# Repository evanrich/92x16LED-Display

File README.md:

#92x16LED-Display

Custom made scrolling LED sign 92 dots wide by 16 tall.

This is going to be the repository for my latest project, a 96x16 LED sign.  

The sign consists of the following:
4x Sure 3216 LED Matrix Displays
1x Custom controller board with bluetooth capabilities to communicate with the Sign
1x Custom power board to deliver 6A to the sign from a 12V source (my car)
Custom cut Acrylic plastic along with various screws to mount and display the sign.

**If you want to see how-to instructions on how to assemble this, please look in the Wiki for a complete guide on how to build this sign**

Please feel free to contact me at evanrich81[at]gmail.com if you have any questions

**UPDATES** <br />
* 5/23/13 - Redesigned controller board. Board sent to fab, uploaded BOM/Datasheets for controller
* 5/5/13 - Created Repository, will begin adding things to it when I have the time.

**Source code, BOMs, Etc**

* https://github.com/evanrich/92x16LED-Display

**Licensing**<br />
<br /><span xmlns:dct="http://purl.org/dc/terms/" property="dct:title">92x16 LED Sign</span> by <a xmlns:cc="http://creativecommons.org/ns#" href="https://github.com/evanrich/Bluetooth-LED-Sign" property="cc:attributionName" rel="cc:attributionURL">Evan Richardson</a> is licensed under a <a rel="license" href="http://creativecommons.org/licenses/by-sa/3.0/">Creative Commons Attribution-ShareAlike 3.0 Unported License</a>.<br />Based on a work at <a xmlns:dct="http://purl.org/dc/terms/" href="https://code.google.com/p/ht1632c/" rel="dct:source">code.google.com</a>.

**Features**

* Small Size: Around 1.5"x2"
* Powered via Vehicle Cigarette plug (other options available)

**Known issues**

* NONE!

**To-Do**

* Work on Documentation
* WOrk on getting BOM's uploaded
* Post everything!

**How You can Help!**

So you want to help contribute and make this better? Awesome!   Here are a few things I could use some help on..

* Will work on this later

**Questions/Support**

* Original library/Sure 3216 information on Arduino.cc Forums @ [http://arduino.cc/forum/index.php?PHPSESSID=f279f2d65aa1a33b09df5ffb6d0332fa&topic=50326.0](http://arduino.cc)

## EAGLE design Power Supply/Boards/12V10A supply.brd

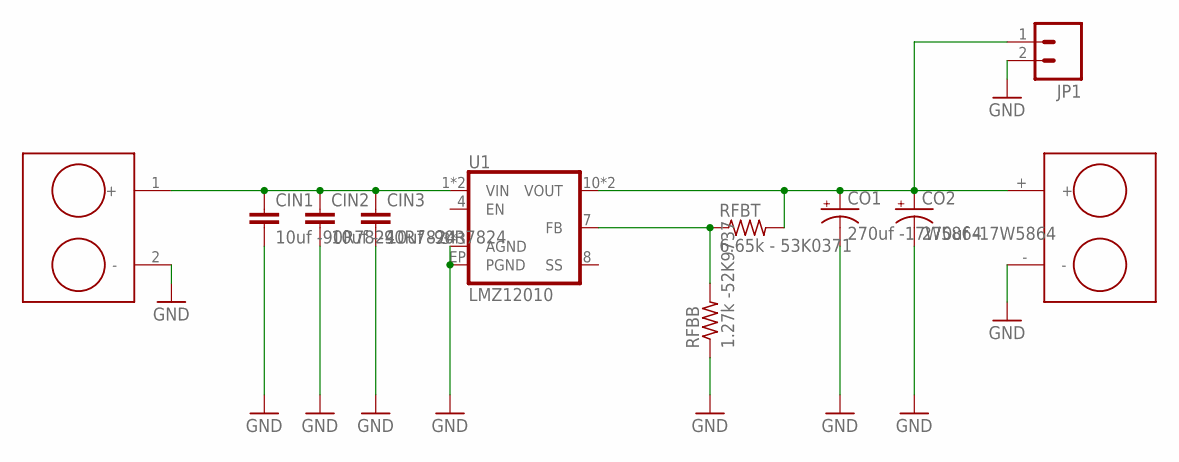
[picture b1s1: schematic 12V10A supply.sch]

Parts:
CIN1, CIN3: 10uf -90R7824; C1210
CIN2: 10uf --90R7824; C1210
CO1, CO2: 270uf -17W5864; JC0CAP
JP1: M02PTH; 1X02
RFBB: 1.27k -52K9737; M0805
RFBT: 6.65k - 53K0371; M0805
U1: LMZ12010; TO-PMOD-11
U$1: 5569-02A2MS-225; 0050362375
VOUTJACK: MC24356; 2PINTERMINAL

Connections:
GND: CIN1.2, CIN2.2, CIN3.2, CO1.-, CO2.-, JP1.2, RFBB.1, U1.3 (AGND), U1.5 (AGND), U1.6 (AGND), U1.EP (PGND), U$1.2 (-), VOUTJACK.-
unnamed: RFBB.2, RFBT.1, U1.7 (FB)
VIN: CIN1.1, CIN2.1, CIN3.1, U1.1 (VIN), U1.2 (VIN), U$1.1 (+)
VOUT: CO1.+, CO2.+, JP1.1, RFBT.2, U1.10 (VOUT), U1.11 (VOUT), VOUTJACK.+

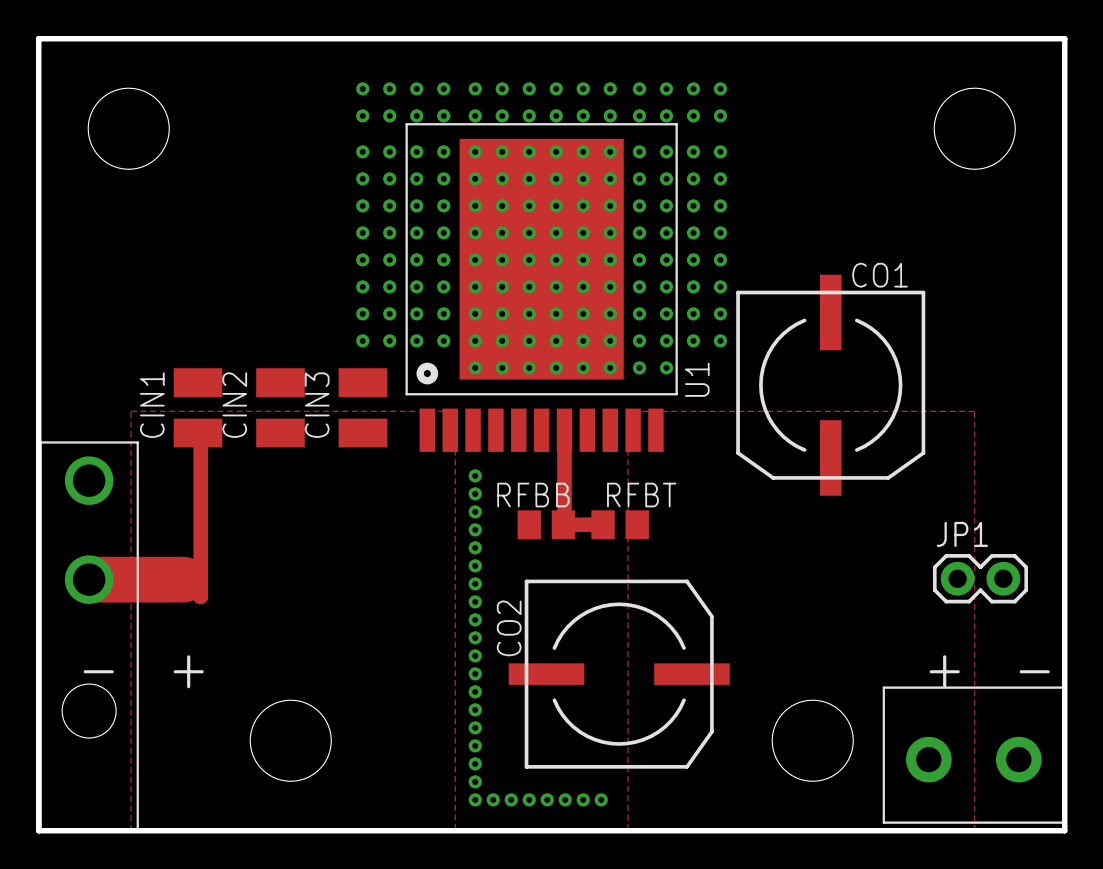
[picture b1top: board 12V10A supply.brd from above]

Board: 2 copper layers, 57.0 x 44.0 mm, 11 parts (0 on the bottom side), 4 nets.

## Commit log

2013-05-02 Added Power supply board and schematic files
2013-05-02 Updated Schematics and Board file Added BOM for Power Supply Added Data sheets for Power Supply
2013-05-08 Added Datasheets for car power cable
2013-05-08 Added front and back images for power board to raw folder.
2013-05-23 Added BOM for SURE Display Controller (Rev. D)
    The boards are at FAB, so this BOM is unproven at this time.
2013-05-23 Added Datasheets for Controller Board (Rev. D)
    Board is at FAB at the moment, so REV D design is unproven

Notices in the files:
parts and their libraries:
SparkFun-Connectors: Licensing: CC v3.0 Share-Alike You are welcome to use this library for commercial purposes.
